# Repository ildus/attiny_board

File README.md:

# attiny_board

This is a little PCB for testing attiny13 chips. I used SMD components (1206 for resistors and LEDs)
and one TL072CN operational amplifier. It was created in Kicad.

# schematic

# how it looks

It could be more prettier but it does its work:

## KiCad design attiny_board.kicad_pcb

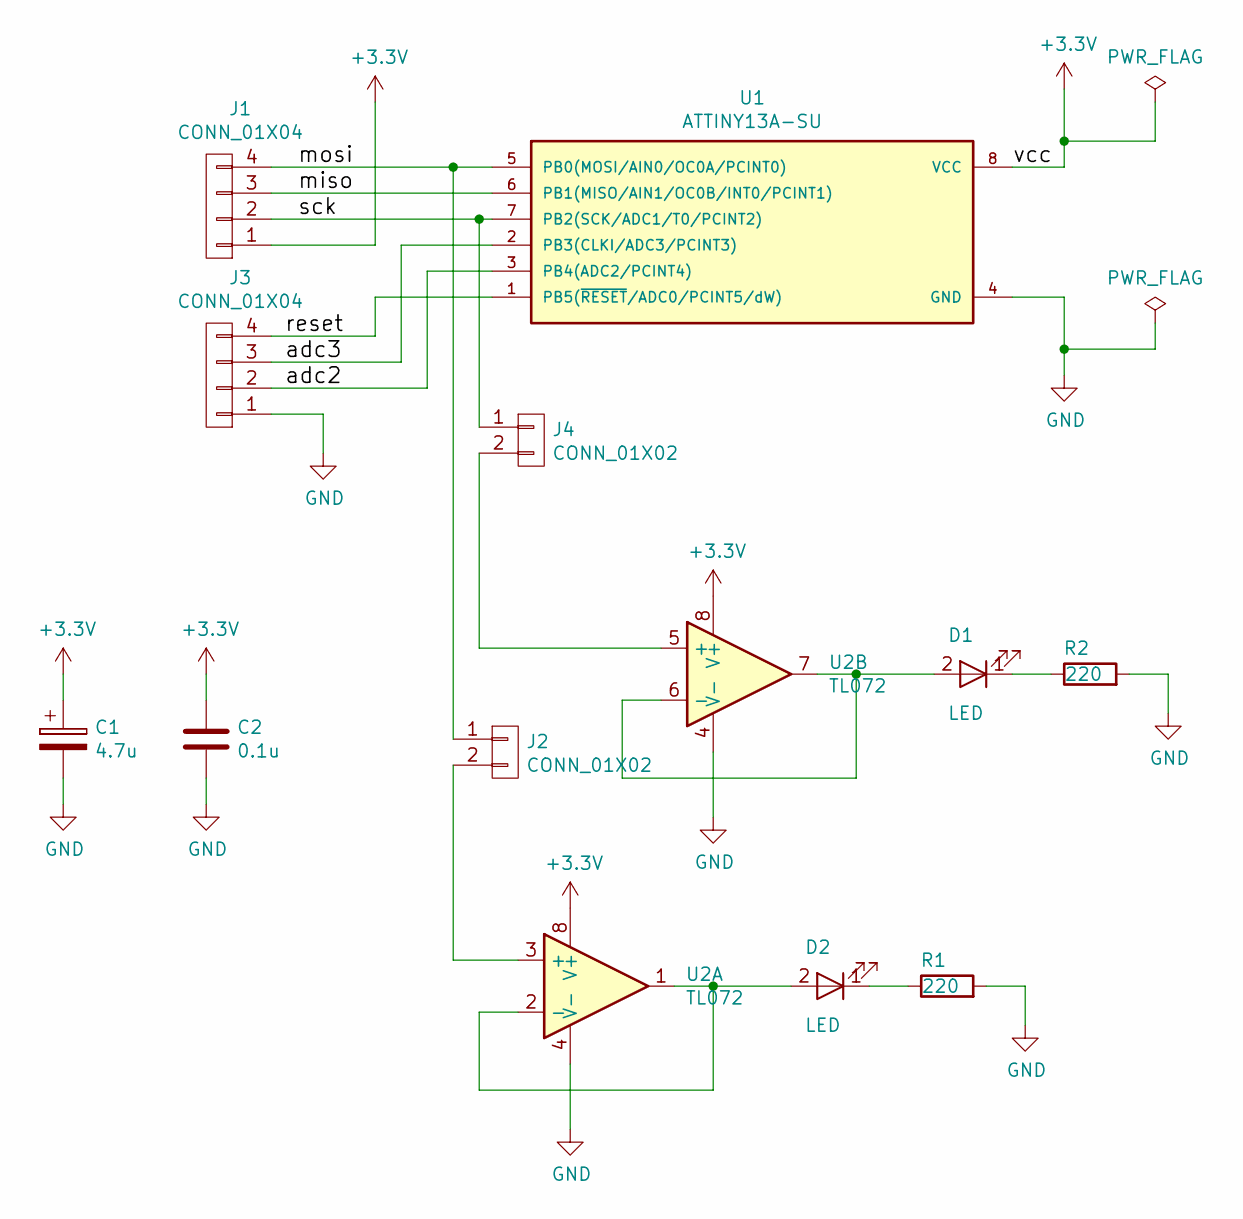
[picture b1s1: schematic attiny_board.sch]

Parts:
C1: 4.7u; CP_Elec_4x4.5
C2: 0.1u; C_0805
D1, D2: LED; LED_1206
J1, J3: CONN_01X04; Molex_KK-6410-04_04x2.54mm_Straight
J2, J4: CONN_01X02; Molex_KK-6410-02_02x2.54mm_Straight
R1, R2: 220; R_1206
U1: ATTINY13A-SU; SOIC-8-N
U2: TL072; DIP-8_W7.62mm

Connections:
+3V3: C1.1, C2.1, J1.1, U1.8 (VCC), U2.8 (V+)
/adc2: J3.2, U1.3 (PB4(ADC2/PCINT4))
/adc3: J3.3, U1.2 (PB3(CLKI/ADC3/PCINT3))
/miso: J1.3, U1.6 (PB1(MISO/AIN1/OC0B/INT0/PCINT1))
/mosi: J1.4, J2.1, U1.5 (PB0(MOSI/AIN0/OC0A/PCINT0))
/reset: J3.4, U1.1 (PB5(~RESET~/ADC0/PCINT5/dW))
/sck: J1.2, J4.1, U1.7 (PB2(SCK/ADC1/T0/PCINT2))
GND: C1.2, C2.2, J3.1, R1.2, R2.2, U1.4 (GND), U2.4 (V-)
unnamed: D1.1 (K), R2.1
unnamed: D1.2 (A), U2.6 (-), U2.7
unnamed: D2.1 (K), R1.1
unnamed: D2.2 (A), U2.1, U2.2 (-)
unnamed: J2.2, U2.3 (+)
unnamed: J4.2, U2.5 (+)

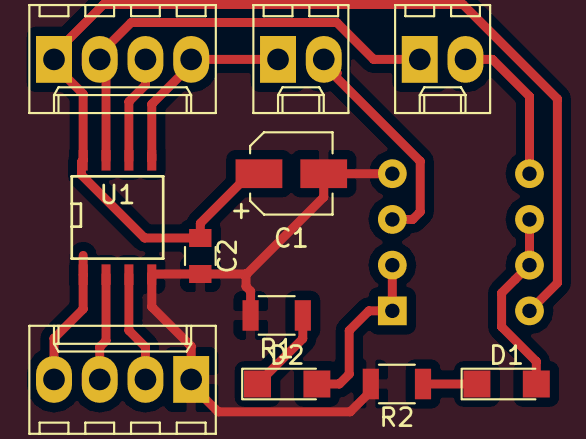
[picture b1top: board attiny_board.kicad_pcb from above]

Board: 2 copper layers, 12 parts (1 on the bottom side), 14 nets.

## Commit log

2017-05-31 initial
